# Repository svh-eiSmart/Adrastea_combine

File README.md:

# Adrastea_combine
Combine Sensor Featherwings data with I2C and SPI to transmit via MQTT to Azure

Current Progress - All I2C sensor driver integration (HIDS, TIDS, ITDS and PADS) for sensor featherwing with basic porting for delay

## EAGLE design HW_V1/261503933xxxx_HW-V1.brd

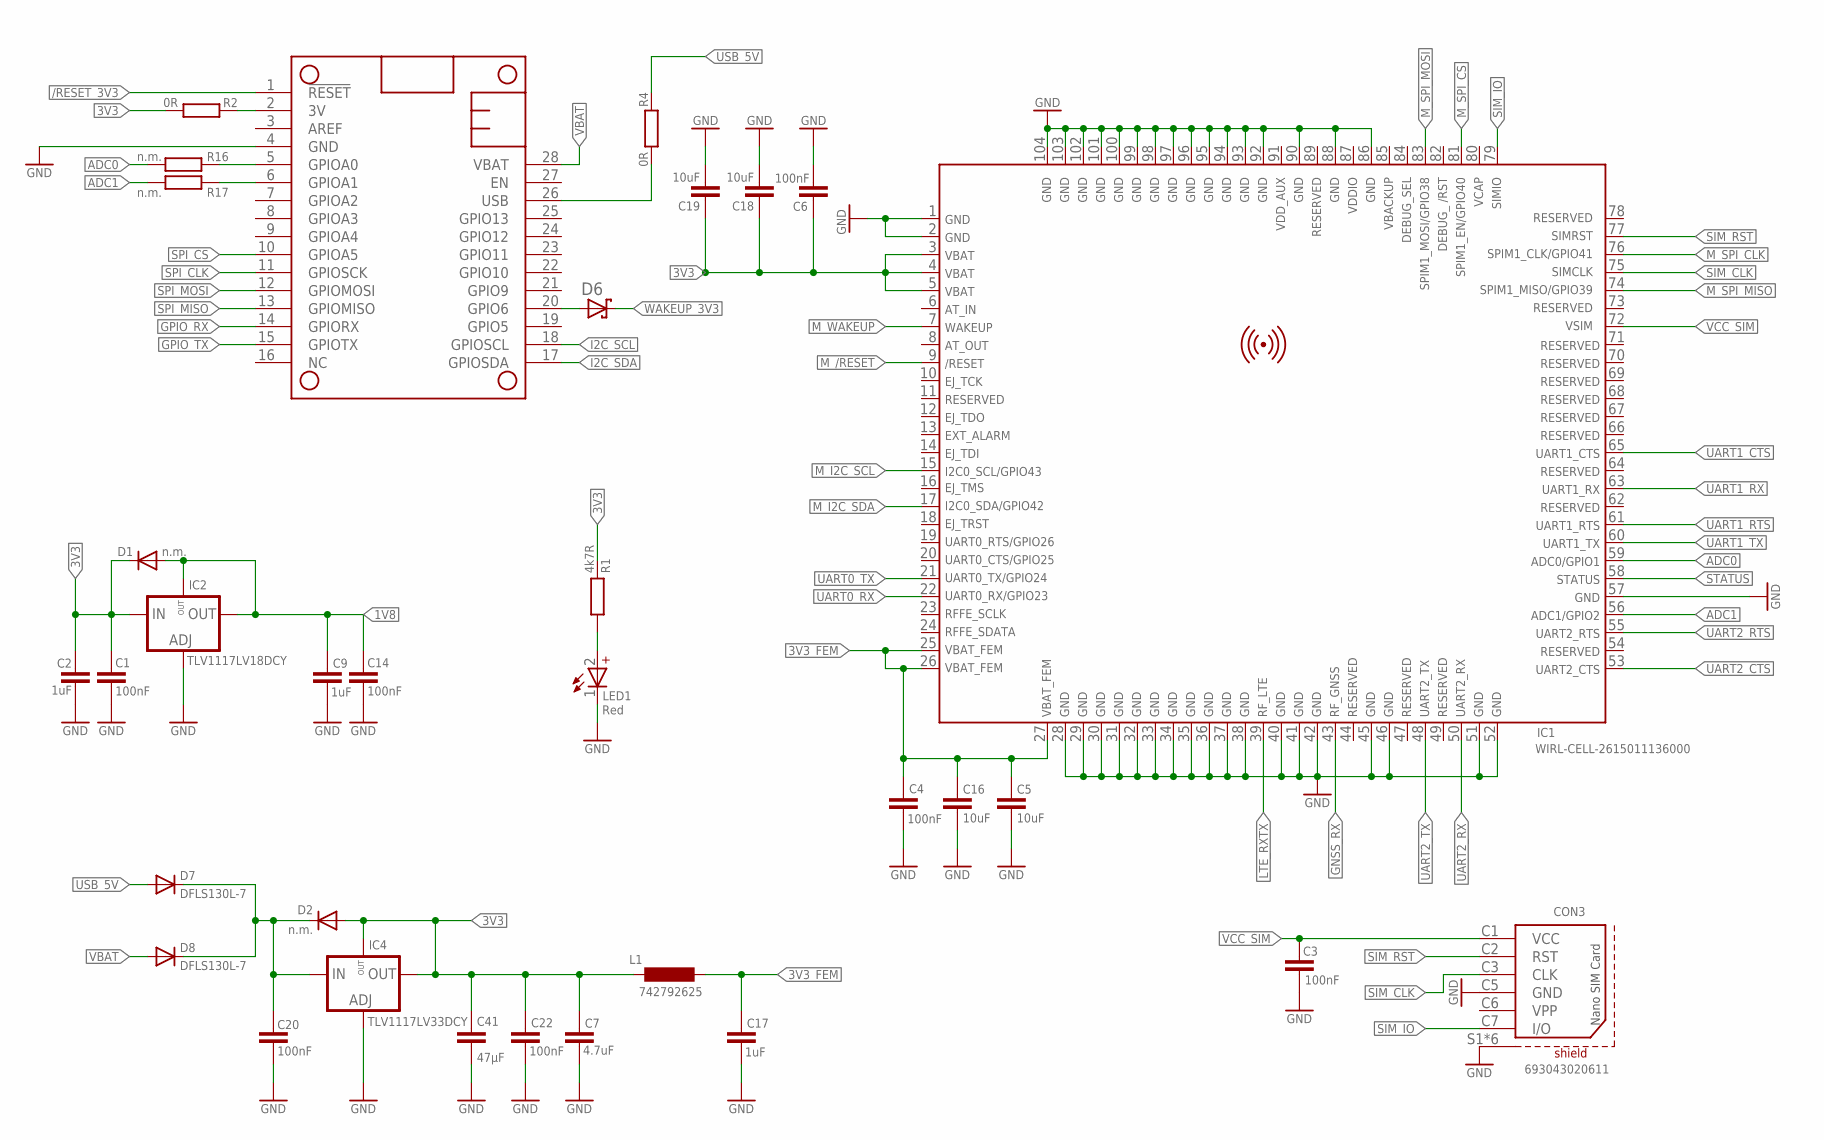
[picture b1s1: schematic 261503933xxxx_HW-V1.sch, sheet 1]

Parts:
C1, C3, C4, C6, C14, C20, C22: 100nF; C0402_IPC
C2, C9, C17: 1uF; C0402_IPC
C5, C16, C18, C19: 10uF; C0402_IPC
C7: 4.7uF; C0402_IPC
C41: 47µF; C0805
CON3: 693043020611
D1, D2: n.m.; SOT23@1
D6: BAT540402_X1-DFN1006-2; X1-DFN1006-2
D7, D8: DFLS130L-7; SOD123_POWERDI
IC1: WIRL-CELL-2615011136000
IC2: TLV1117LV18DCY; SOT223-4
IC4: TLV1117LV33DCY; SOT223-4
L1: 742792625; L0603_WE-MK
LED1: Red; WL-SMSW_1204_A
MS1: FEATHERWING_80MM
R1: 4k7R; R0402_IPC
R2, R4: 0R; R0603_IPC
R16, R17: n.m.; R0402_IPC

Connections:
1V8: C9.1, C14.2, D1.1 (A), IC2.2 (OUT), IC2.4 (OUT); also elsewhere on the board
3V: MS1.2 (3V), R2.2
3V3: C1.2, C2.1, C6.2, C7.1, C18.1, C19.1, C22.2, C41.P$1 (1), D1.3 (C), D2.1 (A), IC1.3 (VBAT), IC1.4 (VBAT), IC1.5 (VBAT), IC2.3 (IN), IC4.2 (OUT), IC4.4 (OUT), L1.1, R1.2, R2.1; also elsewhere on the board
3V3_FEM: C4.2, C5.1, C16.1, C17.1, IC1.25 (VBAT_FEM), IC1.26 (VBAT_FEM), IC1.27 (VBAT_FEM), L1.2
5V_IN: C20.2, D2.3 (C), D7.K (C), D8.K (C), IC4.3 (IN)
/RESET_3V3: MS1.1 (!RESET); also elsewhere on the board
ADC0: IC1.59 (ADC0/GPIO1), R16.1
ADC1: IC1.56 (ADC1/GPIO2), R17.1
ADC_0: MS1.5 (GPIOA0), R16.2
ADC_1: MS1.6 (GPIOA1), R17.2
FEATHER_USB: MS1.26 (USB), R4.1
GND: C1.1, C2.2, C3.2, C4.1, C5.2, C6.1, C7.2, C9.2, C14.1, C16.2, C17.2, C18.2, C19.2, C20.1, C22.1, C41.P$2 (2), CON3.C5 (GND), CON3.S1 (SHIELD), CON3.S2 (SHIELD), CON3.S3 (SHIELD), CON3.S4 (SHIELD), CON3.S5 (SHIELD), CON3.S6 (SHIELD), IC1.1 (GND), IC1.2 (GND), IC1.28 (GND), IC1.29 (GND), IC1.30 (GND), IC1.31 (GND), IC1.32 (GND), IC1.33 (GND), IC1.34 (GND), IC1.35 (GND), IC1.36 (GND), IC1.37 (GND), IC1.38 (GND), IC1.40 (GND), IC1.41 (GND), IC1.42 (GND), IC1.45 (GND), IC1.46 (GND), IC1.51 (GND), IC1.52 (GND), IC1.57 (GND), IC1.86 (GND), IC1.88 (GND), IC1.90 (GND), IC1.92 (GND), IC1.93 (GND), IC1.94 (GND), IC1.95 (GND), IC1.96 (GND), IC1.97 (GND), IC1.98 (GND), IC1.99 (GND), IC1.100 (GND), IC1.101 (GND), IC1.102 (GND), IC1.103 (GND), IC1.104 (GND), IC2.1 (ADJ), IC4.1 (ADJ), LED1.1 (-), MS1.4 (GND); also elsewhere on the board
GNSS_RX: IC1.43 (RF_GNSS_ANT); also elsewhere on the board
GPIO_RX: MS1.14 (GPIORX); also elsewhere on the board
GPIO_TX: MS1.15 (GPIOTX); also elsewhere on the board
I2C_SCL: MS1.18 (GPIOSCL); also elsewhere on the board
I2C_SDA: MS1.17 (GPIOSDA); also elsewhere on the board
LTE_RXTX: IC1.39 (RF_RXTX); also elsewhere on the board
M_/RESET: IC1.9 (/RESET); also elsewhere on the board
M_I2C_SCL: IC1.15 (I2C0_SCL/GPIO43); also elsewhere on the board
M_I2C_SDA: IC1.17 (I2C0_SDA/GPIO42); also elsewhere on the board
M_SPI_CLK: IC1.76 (SPIM1_CLK/GPIO41); also elsewhere on the board
M_SPI_CS: IC1.81 (SPIM1_EN/GPIO40); also elsewhere on the board
M_SPI_MISO: IC1.74 (SPIM1_MISO/GPIO39); also elsewhere on the board
M_SPI_MOSI: IC1.83 (SPIM1_MOSI/GPIO38); also elsewhere on the board
M_WAKEUP: IC1.7 (WAKEUP); also elsewhere on the board
unnamed: LED1.2 (+), R1.1
unnamed: D6.2 (A), MS1.20 (GPIO6)
SIM_CLK: CON3.C3 (CLK), IC1.75 (SIMCLK)
SIM_IO: CON3.C7 (I/O), IC1.79 (SIMIO)
SIM_RST: CON3.C2 (RST), IC1.77 (SIMRST)
SPI_CLK: MS1.11 (GPIOSCK); also elsewhere on the board
SPI_CS: MS1.10 (GPIOA5); also elsewhere on the board
SPI_MISO: MS1.13 (GPIOMISO); also elsewhere on the board
SPI_MOSI: MS1.12 (GPIOMOSI); also elsewhere on the board
STATUS: IC1.58 (STATUS); also elsewhere on the board
UART0_RX: IC1.22 (UART0_RX/GPIO23); also elsewhere on the board
UART0_TX: IC1.21 (UART0_TX/GPIO24); also elsewhere on the board
UART1_CTS: IC1.65 (UART1_CTS); also elsewhere on the board
UART1_RTS: IC1.61 (UART1_RTS); also elsewhere on the board
UART1_RX: IC1.63 (UART1_RX); also elsewhere on the board
UART1_TX: IC1.60 (UART1_TX); also elsewhere on the board
UART2_CTS: IC1.53 (UART2_CTS); also elsewhere on the board
UART2_RTS: IC1.55 (UART2_RTS); also elsewhere on the board
UART2_RX: IC1.50 (UART2_RX); also elsewhere on the board
UART2_TX: IC1.48 (UART2_TX); also elsewhere on the board
USB_5V: D7.A, R4.2; also elsewhere on the board
VBAT: D8.A, MS1.28 (VBAT); also elsewhere on the board
VCC_SIM: C3.1, CON3.C1 (VCC), IC1.72 (VSIM)
WAKEUP_3V3: D6.1 (C); also elsewhere on the board

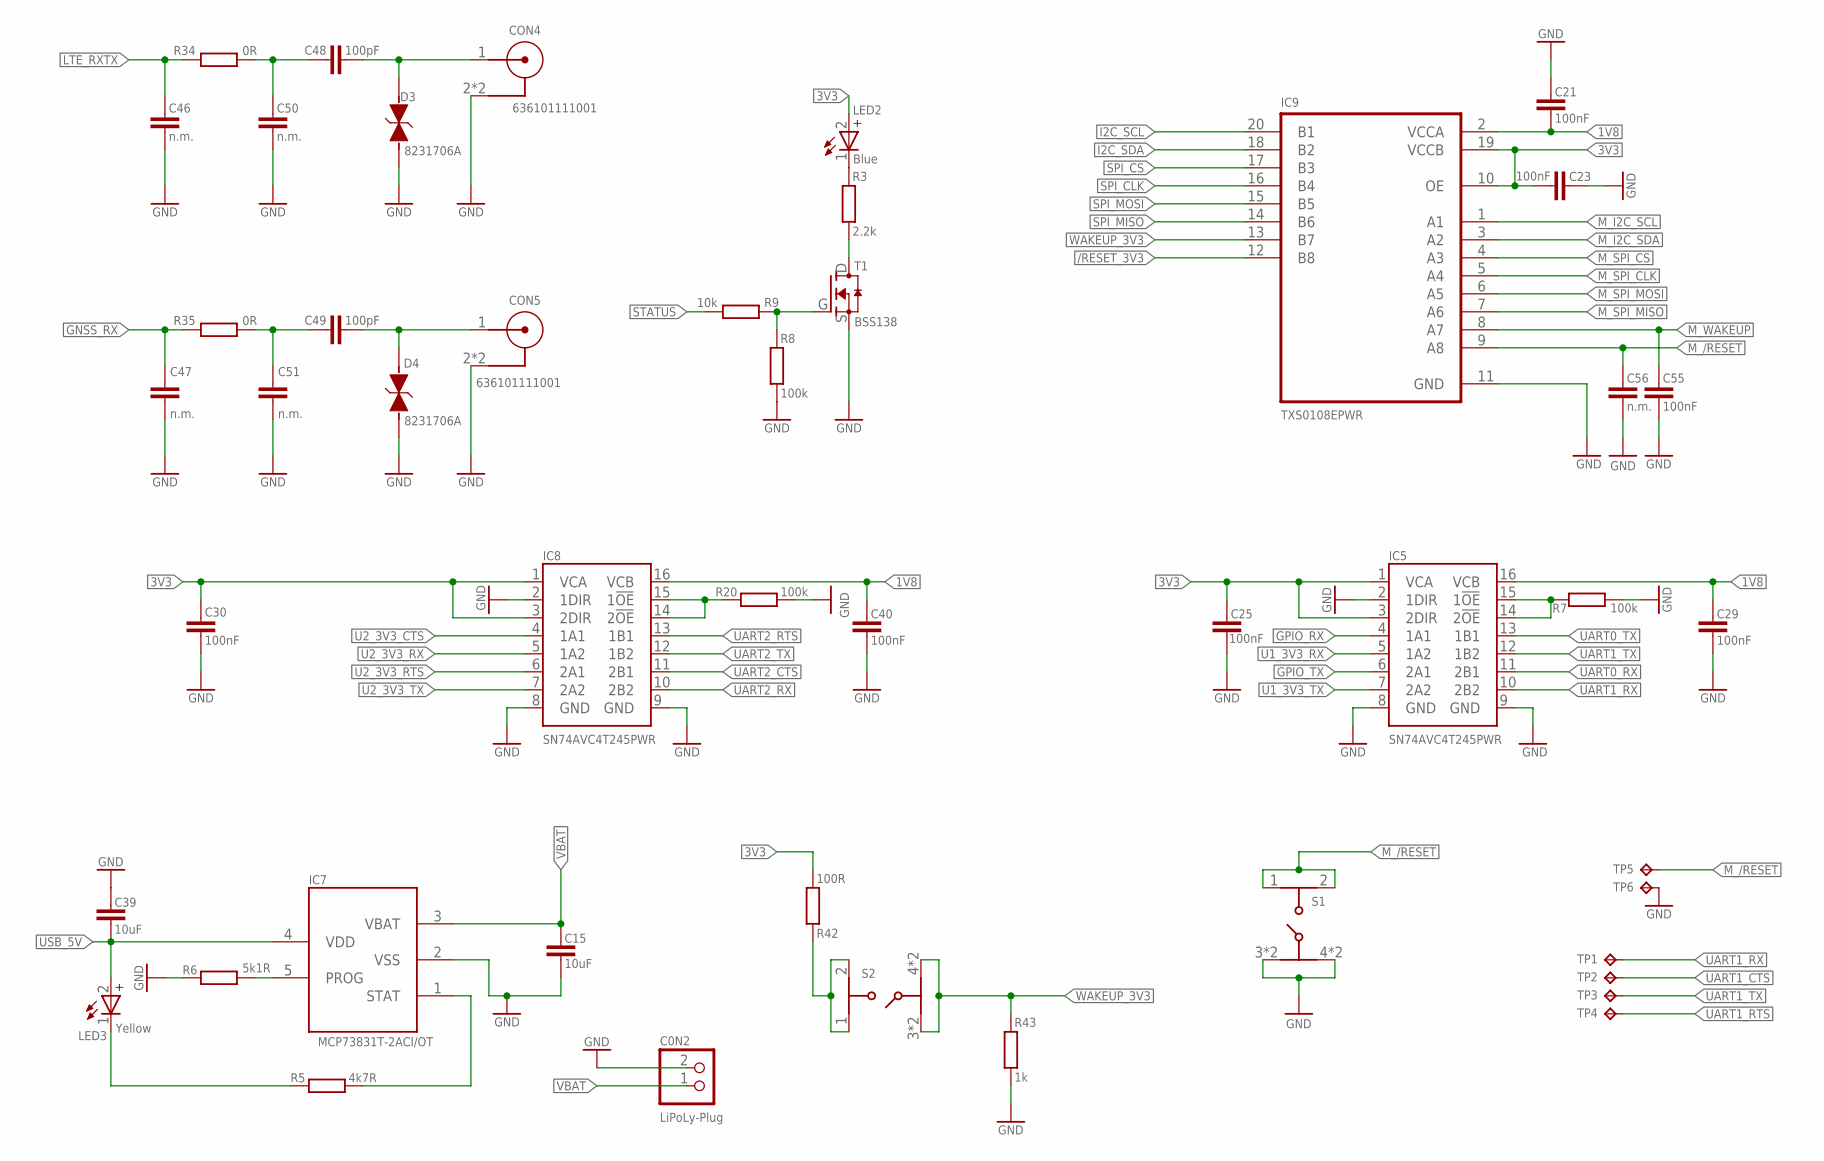
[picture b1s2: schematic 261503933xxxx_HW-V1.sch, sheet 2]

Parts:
C0N2: LiPoLy-Plug; JST-PH-2-SMT-RA-ADRASTEA-ANGEPASST
C15: 10uF; C0402_IPC
C21, C23, C25, C29, C30, C40, C55: 100nF; C0402_IPC
C39: 10uF; C0603_IPC
C46, C47, C50, C51, C56: n.m.; C0402_IPC
C48, C49: 100pF; C0402_IPC
CON4, CON5: 636101111001
D3, D4: 8231706A; WE-VE_FEMTOF_0402
IC5, IC8: SN74AVC4T245PWR; PW16(TSSOP16)
IC7: MCP73831T-2ACI/OT; SOT23-5
IC9: TXS0108EPWR; SOP65P640X120-20N
LED2: Blue; WL-SMSW_1204_A
LED3: Yellow; WL-SMSW_1204_A
R3: 2.2k; R0402_IPC
R5: 4k7R; R0402_IPC
R6: 5k1R; R0402_IPC
R7, R8, R20: 100k; R0402_IPC
R9: 10k; R0402_IPC
R34, R35: 0R; R0402_IPC
R42: 100R; R0402_IPC
R43: 1k; R0402_IPC
S1, S2: 434331013822
T1: BSS138
TP1, TP2, TP3, TP4, TP5, TP6: TP15R

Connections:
1V8: C21.1, C29.2, C40.2, IC5.16 (VCB), IC8.16 (VCB), IC9.2 (VCCA); also elsewhere on the board
3V3: C23.1, C25.2, C30.2, IC5.1 (VCA), IC5.3 (2DIR), IC8.1 (VCA), IC8.3 (2DIR), IC9.10 (OE), IC9.19 (VCCB), LED2.2 (+), R42.1; also elsewhere on the board
/RESET_3V3: IC9.12 (B8); also elsewhere on the board
GND: C0N2.2 (1), C15.2, C21.2, C23.2, C25.1, C29.1, C30.1, C39.1, C40.1, C46.1, C47.1, C50.1, C51.1, C55.1, C56.1, CON4.2, CON4.3 (2), CON5.2, CON5.3 (2), D3.2, D4.2, IC5.2 (1DIR), IC5.8 (GND), IC5.9 (GND), IC7.2 (VSS), IC8.2 (1DIR), IC8.8 (GND), IC8.9 (GND), IC9.11 (GND), R6.1, R7.2, R8.2, R20.2, R43.2, S1.3, S1.4, S1.5 (3), S1.6 (4), T1.S, TP6.P$1; also elsewhere on the board
GNSS_RX: C47.2, R35.2; also elsewhere on the board
GPIO_RX: IC5.4 (1A1); also elsewhere on the board
GPIO_TX: IC5.6 (2A1); also elsewhere on the board
I2C_SCL: IC9.20 (B1); also elsewhere on the board
I2C_SDA: IC9.18 (B2); also elsewhere on the board
LS_ISO_CTRL1: IC8.14 (2!OE), IC8.15 (1!OE), R20.1
LTE_RXTX: C46.2, R34.2; also elsewhere on the board
M_/RESET: C56.2, IC9.9 (A8), S1.1, S1.2, TP5.P$1; also elsewhere on the board
M_I2C_SCL: IC9.1 (A1); also elsewhere on the board
M_I2C_SDA: IC9.3 (A2); also elsewhere on the board
M_SPI_CLK: IC9.5 (A4); also elsewhere on the board
M_SPI_CS: IC9.4 (A3); also elsewhere on the board
M_SPI_MISO: IC9.7 (A6); also elsewhere on the board
M_SPI_MOSI: IC9.6 (A5); also elsewhere on the board
M_WAKEUP: C55.2, IC9.8 (A7); also elsewhere on the board
unnamed: LED2.1 (-), R3.1
unnamed: C49.1, CON5.1, D4.1
unnamed: C48.1, CON4.1, D3.1
unnamed: R42.2, S2.1, S2.2
unnamed: C48.2, C50.2, R34.1
unnamed: R3.2, T1.D
unnamed: C49.2, C51.2, R35.1
unnamed: R8.1, R9.2, T1.G
unnamed: LED3.1 (-), R5.1
unnamed: IC7.5 (PROG), R6.2
unnamed: IC5.14 (2!OE), IC5.15 (1!OE), R7.1
SPI_CLK: IC9.16 (B4); also elsewhere on the board
SPI_CS: IC9.17 (B3); also elsewhere on the board
SPI_MISO: IC9.14 (B6); also elsewhere on the board
SPI_MOSI: IC9.15 (B5); also elsewhere on the board
STAT: IC7.1 (STAT), R5.2
STATUS: R9.1; also elsewhere on the board
U1_3V3_RX: IC5.5 (1A2); also elsewhere on the board
U1_3V3_TX: IC5.7 (2A2); also elsewhere on the board
U2_3V3_CTS: IC8.4 (1A1); also elsewhere on the board
U2_3V3_RTS: IC8.6 (2A1); also elsewhere on the board
U2_3V3_RX: IC8.5 (1A2); also elsewhere on the board
U2_3V3_TX: IC8.7 (2A2); also elsewhere on the board
UART0_RX: IC5.11 (2B1); also elsewhere on the board
UART0_TX: IC5.13 (1B1); also elsewhere on the board
UART1_CTS: TP2.P$1; also elsewhere on the board
UART1_RTS: TP4.P$1; also elsewhere on the board
UART1_RX: IC5.10 (2B2), TP1.P$1; also elsewhere on the board
UART1_TX: IC5.12 (1B2), TP3.P$1; also elsewhere on the board
UART2_CTS: IC8.11 (2B1); also elsewhere on the board
UART2_RTS: IC8.13 (1B1); also elsewhere on the board
UART2_RX: IC8.10 (2B2); also elsewhere on the board
UART2_TX: IC8.12 (1B2); also elsewhere on the board
USB_5V: C39.2, IC7.4 (VDD), LED3.2 (+); also elsewhere on the board
VBAT: C0N2.1 (2), C15.1, IC7.3 (VBAT); also elsewhere on the board
WAKEUP_3V3: IC9.13 (B7), R43.1, S2.3, S2.4, S2.5 (3), S2.6 (4); also elsewhere on the board

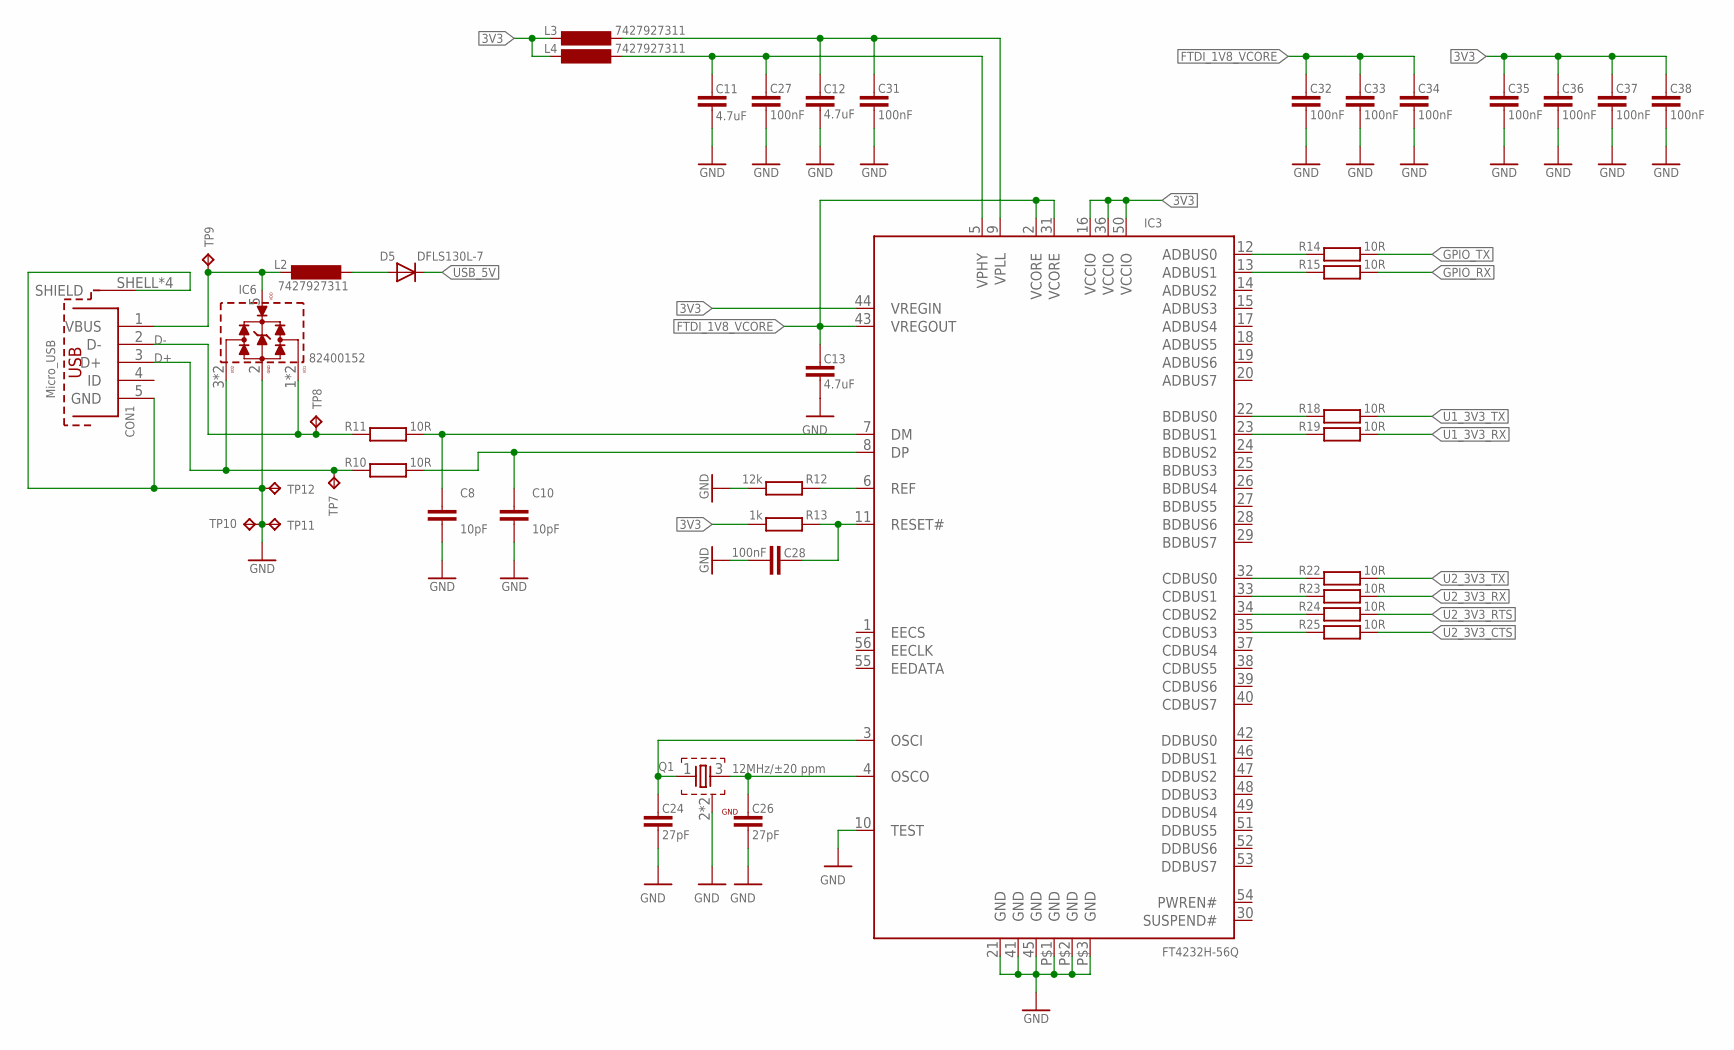
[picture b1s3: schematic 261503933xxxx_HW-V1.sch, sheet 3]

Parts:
C8, C10: 10pF; C0402_IPC
C11, C12, C13: 4.7uF; C0402_IPC
C24, C26: 27pF; C0402_IPC
C27, C28, C31, C32, C33, C34, C35, C36, C37, C38: 100nF; C0402_IPC
CON1: Micro_USB; 629105150521
D5: DFLS130L-7; SOD123_POWERDI
IC3: FT4232H-56Q; VQFN-56
IC6: 82400152; WE-TVS_SOT563
L2, L3, L4: 7427927311; L0402_WE-MK
Q1: 12MHz/±20 ppm; WE-XTAL_CFPX-180
R10, R11, R14, R15, R18, R19, R22, R23, R24, R25: 10R; R0402_IPC
R12: 12k; R0402_IPC
R13: 1k; R0402_IPC
TP7, TP8, TP9, TP10, TP11, TP12: TP15R

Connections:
3V3: C35.2, C36.2, C37.2, C38.2, IC3.16 (VCCIO), IC3.36 (VCCIO), IC3.44 (VREGIN), IC3.50 (VCCIO), L3.P$2 (2), L4.P$2 (2), R13.1; also elsewhere on the board
D+: CON1.3 (D+), IC6.3 (I/O2), IC6.4 (I/O2), R10.1, TP7.P$1
D-: CON1.2 (D-), IC6.1 (I/O1), IC6.6 (I/O1), R11.2, TP8.P$1
FTDI_1V8_VCORE: C13.1, C32.2, C33.2, C34.2, IC3.2 (VCORE), IC3.31 (VCORE), IC3.43 (VREGOUT)
FTDI_CTS#_CH-C: IC3.35 (CDBUS3), R25.1
FTDI_RESET: C28.2, IC3.11 (RESET#), R13.2
FTDI_RTS#_CH-C: IC3.34 (CDBUS2), R24.1
FTDI_RXD_CH-A: IC3.13 (ADBUS1), R15.1
FTDI_RXD_CH-B: IC3.23 (BDBUS1), R19.1
FTDI_RXD_CH-C: IC3.33 (CDBUS1), R23.1
FTDI_TXD_CH-A: IC3.12 (ADBUS0), R14.1
FTDI_TXD_CH-B: IC3.22 (BDBUS0), R18.1
FTDI_TXD_CH-C: IC3.32 (CDBUS0), R22.1
GND: C8.1, C10.1, C11.2, C12.2, C13.2, C24.1, C26.1, C27.1, C28.1, C31.1, C32.1, C33.1, C34.1, C35.1, C36.1, C37.1, C38.1, CON1.5 (GND), CON1.SHELL (SHIELD), CON1.SHELL1 (SHIELD), CON1.SHELL2 (SHIELD), CON1.SHELL3 (SHIELD), IC3.10 (TEST), IC3.21 (GND), IC3.41 (GND), IC3.45 (GND), IC3.P$1 (GND), IC3.P$2 (GND), IC3.P$3 (GND), IC6.2 (GND), Q1.2 (GND), Q1.4 (GND), R12.1, TP10.P$1, TP11.P$1, TP12.P$1; also elsewhere on the board
GPIO_RX: R15.2; also elsewhere on the board
GPIO_TX: R14.2; also elsewhere on the board
unnamed: C8.2, IC3.7 (DM), R11.1
unnamed: C10.2, IC3.8 (DP), R10.2
unnamed: D5.A, L2.P$1 (1)
unnamed: C11.1, C27.2, IC3.5 (VPHY), L4.P$1 (1)
unnamed: C12.1, C31.2, IC3.9 (VPLL), L3.P$1 (1)
unnamed: IC3.6 (REF), R12.2
unnamed: C24.2, IC3.3 (OSCI), Q1.1
unnamed: C26.2, IC3.4 (OSCO), Q1.3 (2)
U1_3V3_RX: R19.2; also elsewhere on the board
U1_3V3_TX: R18.2; also elsewhere on the board
U2_3V3_CTS: R25.2; also elsewhere on the board
U2_3V3_RTS: R24.2; also elsewhere on the board
U2_3V3_RX: R23.2; also elsewhere on the board
U2_3V3_TX: R22.2; also elsewhere on the board
USB_5V: D5.K (C); also elsewhere on the board
VBUS: CON1.1 (VBUS), IC6.5 (VDD), L2.P$2 (2), TP9.P$1

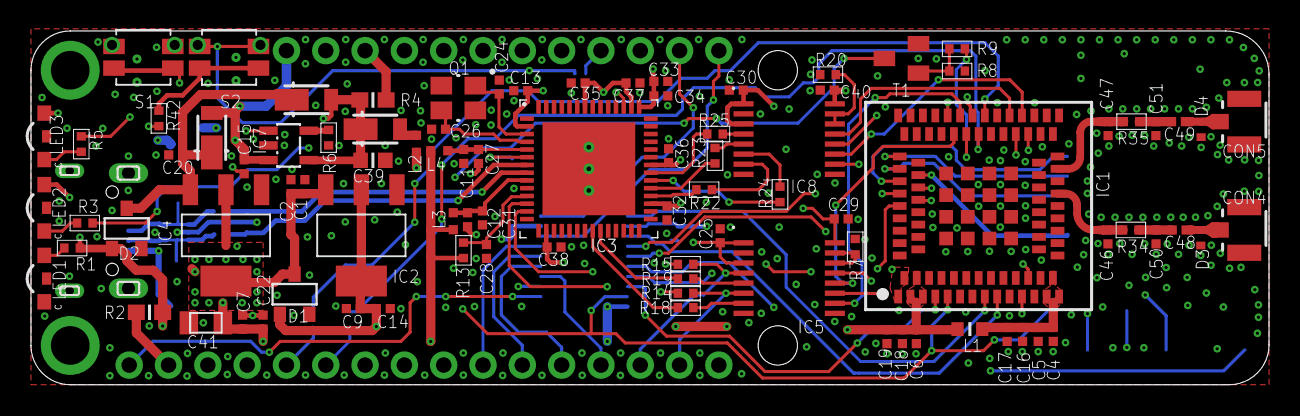
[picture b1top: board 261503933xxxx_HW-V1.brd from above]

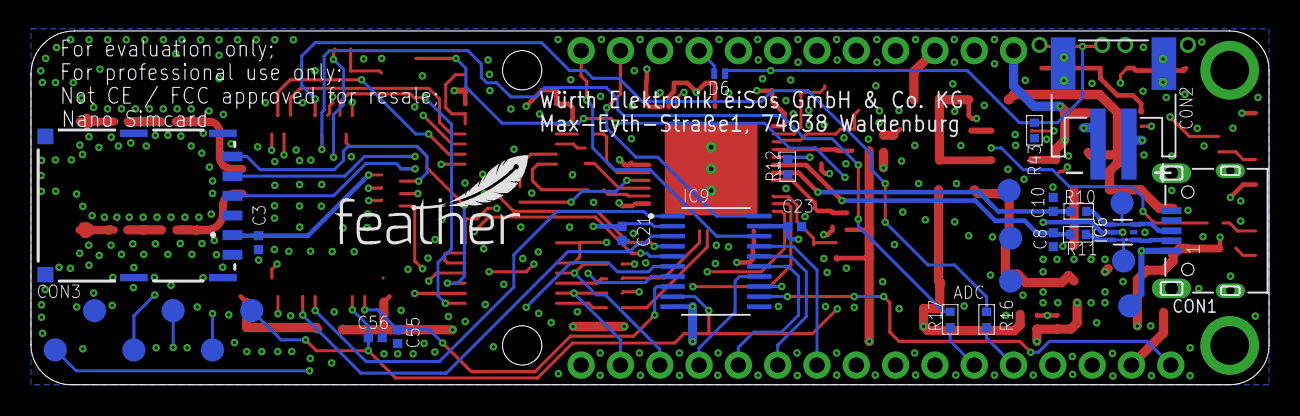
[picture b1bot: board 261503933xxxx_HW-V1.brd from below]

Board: 4 copper layers, 79.9 x 22.7 mm, 124 parts (32 on the bottom side), 90 nets.

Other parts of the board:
U$4: FEATHER_12MM

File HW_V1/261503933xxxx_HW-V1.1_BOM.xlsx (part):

Part | Value | NR | MANUFACTURER | COMMENT | Device | Package | Description | CCH-TYP | COMMENT2 | DATASHEET-URL | DESCRIPTION3 | GENDER | GERDER | HEIGHT | HERSTELLER | ILEAK | ISAT | Spalte4 | MANUFACTURER2 | MAT | MF | MOUNT | MP | Spalte5 | NR2 | P | PACK | PACKAGE6 | PART-NUMBER | PINS | PRICE | RDC | SPG | TEMP | TOL | TYPE | VALUE | VCH-TYP | VESD-AIR | VESD-CONTACT | Z
C0N2 | LiPoLy-Plug | 1769 | Adafruit |  | JST_2PIN | JST-PH-2-SMT-RA-ADRASTEA-ANGEPASST | JST 2-Pin Connectors of various flavors |  |  |  |  |  |  | 9mm |  |  |  |  |  |  |  |  |  |  |  |  | SMT
C1 | 100nF | 885012205037 | Würth Elektronik |  | C0402_IPC | C0402_IPC |  |  |  |  |  |  |  | 0.5mm |  |  |  |  |  | X7R |  |  |  |  |  |  | 402 |  |  |  |  |  | 16V |  | 0.1
C10 | 10pF | 885012005055 | Würth Elektronik |  | C10PF0402_IPC | C0402_IPC |  |  |  |  |  |  |  | 0.5mm |  |  |  |  |  | NP0 |  |  |  |  |  |  | 402 |  |  |  |  |  | 50V |  | 0.05
C11 | 4.7uF | 885012105008 | Würth Elektronik |  | C4.7UF0402_IPC | C0402_IPC |  |  |  |  |  |  |  | 0.5mm |  |  |  |  |  | X5R |  |  |  |  |  |  | 402 |  |  |  |  |  | 6.3V |  | 0.2
C12 | 4.7uF | 885012105008 | Würth Elektronik |  | C4.7UF0402_IPC | C0402_IPC |  |  |  |  |  |  |  | 0.5mm |  |  |  |  |  | X5R |  |  |  |  |  |  | 402 |  |  |  |  |  | 6.3V |  | 0.2
C13 | 4.7uF | 885012105008 | Würth Elektronik |  | C4.7UF0402_IPC | C0402_IPC |  |  |  |  |  |  |  | 0.5mm |  |  |  |  |  | X5R |  |  |  |  |  |  | 402 |  |  |  |  |  | 6.3V |  | 0.2
C14 | 100nF | 885012205037 | Würth Elektronik |  | C0402_IPC | C0402_IPC |  |  |  |  |  |  |  | 0.5mm |  |  |  |  |  | X7R |  |  |  |  |  |  | 402 |  |  |  |  |  | 16V |  | 0.1
C15 | 10uF | 885012105020 | Würth Elektronik |  | C10UF0402_IPC | C0402_IPC |  |  |  |  |  |  |  | 0.5mm |  |  |  |  |  | X5R |  |  |  |  |  |  | 402 |  |  |  |  |  | 6.3V | -55 to +85°c | 0.2
C16 | 10uF | 885012105020 | Würth Elektronik |  | C0402_IPC | C0402_IPC |  |  |  |  |  |  |  | 0.5mm |  |  |  |  |  | X5R | 0.2 |  |  |  |  |  | 402 |  |  |  |  |  | 6,3V |  | 0.2
C17 | 1uF | 885012105012 | Würth Elektronik |  | C1UF0402_IPC | C0402_IPC |  |  |  |  |  |  |  | 0.5mm |  |  |  |  |  | X5R |  |  |  |  |  |  | 402 |  |  |  |  |  | 10V |  | 0.2
C18 | 10uF | 885012105020 | Würth Elektronik |  | C0402_IPC | C0402_IPC |  |  |  |  |  |  |  | 0.5mm |  |  |  |  |  | X5R | 0.2 |  |  |  |  |  | 402 |  |  |  |  |  | 6,3V |  | 0.2
C19 | 10uF | 885012105020 | Würth Elektronik |  | C0402_IPC | C0402_IPC |  |  |  |  |  |  |  | 0.5mm |  |  |  |  |  | X5R | 0.2 |  |  |  |  |  | 402 |  |  |  |  |  | 6,3V |  | 0.2
C2 | 1uF | 885012105012 | Würth Elektronik |  | C1UF0402_IPC | C0402_IPC |  |  |  |  |  |  |  | 0.5mm |  |  |  |  |  | X5R |  |  |  |  |  |  | 402 |  |  |  |  |  | 10V |  | 0.2
C20 | 100nF | 885012205037 | Würth Elektronik |  | C0402_IPC | C0402_IPC |  |  |  |  |  |  |  | 0.5mm |  |  |  |  |  | X7R |  |  |  |  |  |  | 402 |  |  |  |  |  | 16V |  | 0.1
C21 | 100nF | 885012205037 | Würth Elektronik |  | C0402_IPC | C0402_IPC |  |  |  |  |  |  |  | 0.5mm |  |  |  |  |  | X7R |  |  |  |  |  |  | 402 |  |  |  |  |  | 16V |  | 0.1
C22 | 100nF | 885012205037 | Würth Elektronik |  | C0402_IPC | C0402_IPC |  |  |  |  |  |  |  | 0.5mm |  |  |  |  |  | X7R |  |  |  |  |  |  | 402 |  |  |  |  |  | 16V |  | 0.1
C23 | 100nF | 885012205037 | Würth Elektronik |  | C0402_IPC | C0402_IPC |  |  |  |  |  |  |  | 0.5mm |  |  |  |  |  | X7R |  |  |  |  |  |  | 402 |  |  |  |  |  | 16V |  | 0.1
C24 | 27pF | CL05C270JB5NNNC | Samsung |  | C27P0402_IPC | C0402_IPC |  |  |  |  |  |  |  | 0.5mm |  |  |  |  |  | C0G |  |  |  |  |  |  | 402 |  |  |  |  |  | 50V |  | 0.05
C25 | 100nF | 885012205037 | Würth Elektronik |  | C0402_IPC | C0402_IPC |  |  |  |  |  |  |  | 0.5mm |  |  |  |  |  | X7R |  |  |  |  |  |  | 402 |  |  |  |  |  | 16V |  | 0.1
C26 | 27pF | CL05C270JB5NNNC | Samsung |  | C27P0402_IPC | C0402_IPC |  |  |  |  |  |  |  | 0.5mm |  |  |  |  |  | C0G |  |  |  |  |  |  | 402 |  |  |  |  |  | 50V |  | 0.05
C27 | 100nF | 885012205037 | Würth Elektronik |  | C0402_IPC | C0402_IPC |  |  |  |  |  |  |  | 0.5mm |  |  |  |  |  | X7R |  |  |  |  |  |  | 402 |  |  |  |  |  | 16V |  | 0.1
C28 | 100nF | 885012205037 | Würth Elektronik |  | C0402_IPC | C0402_IPC |  |  |  |  |  |  |  | 0.5mm |  |  |  |  |  | X7R |  |  |  |  |  |  | 402 |  |  |  |  |  | 16V |  | 0.1
C29 | 100nF | 885012205037 | Würth Elektronik |  | C0402_IPC | C0402_IPC |  |  |  |  |  |  |  | 0.5mm |  |  |  |  |  | X7R |  |  |  |  |  |  | 402 |  |  |  |  |  | 16V |  | 0.1
C3 | 100nF | 885012205037 | Würth Elektronik |  | C100NF0402_IPC | C0402_IPC |  |  |  |  |  |  |  | 0.5mm |  |  |  |  |  | X7R |  |  |  |  |  |  | 402 |  |  |  |  |  | 16V | -55 to +125°C | 0.1
C30 | 100nF | 885012205037 | Würth Elektronik |  | C0402_IPC | C0402_IPC |  |  |  |  |  |  |  | 0.5mm |  |  |  |  |  | X7R |  |  |  |  |  |  | 402 |  |  |  |  |  | 16V |  | 0.1
C31 | 100nF | 885012205037 | Würth Elektronik |  | C0402_IPC | C0402_IPC |  |  |  |  |  |  |  | 0.5mm |  |  |  |  |  | X7R |  |  |  |  |  |  | 402 |  |  |  |  |  | 16V |  | 0.1
C32 | 100nF | 885012205037 | Würth Elektronik |  | C0402_IPC | C0402_IPC |  |  |  |  |  |  |  | 0.5mm |  |  |  |  |  | X7R |  |  |  |  |  |  | 402 |  |  |  |  |  | 16V |  | 0.1
C33 | 100nF | 885012205037 | Würth Elektronik |  | C0402_IPC | C0402_IPC |  |  |  |  |  |  |  | 0.5mm |  |  |  |  |  | X7R |  |  |  |  |  |  | 402 |  |  |  |  |  | 16V |  | 0.1
C34 | 100nF | 885012205037 | Würth Elektronik |  | C0402_IPC | C0402_IPC |  |  |  |  |  |  |  | 0.5mm |  |  |  |  |  | X7R |  |  |  |  |  |  | 402 |  |  |  |  |  | 16V |  | 0.1
C35 | 100nF | 885012205037 | Würth Elektronik |  | C0402_IPC | C0402_IPC |  |  |  |  |  |  |  | 0.5mm |  |  |  |  |  | X7R |  |  |  |  |  |  | 402 |  |  |  |  |  | 16V |  | 0.1
C36 | 100nF | 885012205037 | Würth Elektronik |  | C0402_IPC | C0402_IPC |  |  |  |  |  |  |  | 0.5mm |  |  |  |  |  | X7R |  |  |  |  |  |  | 402 |  |  |  |  |  | 16V |  | 0.1
C37 | 100nF | 885012205037 | Würth Elektronik |  | C0402_IPC | C0402_IPC |  |  |  |  |  |  |  | 0.5mm |  |  |  |  |  | X7R |  |  |  |  |  |  | 402 |  |  |  |  |  | 16V |  | 0.1
C38 | 100nF | 885012205037 | Würth Elektronik |  | C0402_IPC | C0402_IPC |  |  |  |  |  |  |  | 0.5mm |  |  |  |  |  | X7R |  |  |  |  |  |  | 402 |  |  |  |  |  | 16V |  | 0.1
C39 | 10uF | 885012106031 | Wurth Elektronik |  | C1UF0603_IPC | C0603_IPC |  |  |  |  |  |  |  | 0.8mm |  |  |  |  |  | X5R |  |  |  |  |  |  | 603 |  |  |  |  |  | 25V |  | 0.1
C4 | 100nF | 885012205037 | Würth Elektronik |  | C0402_IPC | C0402_IPC |  |  |  |  |  |  |  | 0.5mm |  |  |  |  |  | X7R |  |  |  |  |  |  | 402 |  |  |  |  |  | 16V |  | 0.1
C40 | 100nF | 885012205037 | Würth Elektronik |  | C0402_IPC | C0402_IPC |  |  |  |  |  |  |  | 0.5mm |  |  |  |  |  | X7R |  |  |  |  |  |  | 402 |  |  |  |  |  | 16V |  | 0.1
C41 | 47µF | 885012107006 | Wurth Elektronik |  | C47UF0805 | C0805 |  |  |  |  |  |  |  | 1.25mm |  |  |  |  |  | X7R |  |  |  |  |  |  | 805 |  |  |  |  |  | 6.3V |  | 0.2
C46 | n.m. | n.m. | n.m. |  | C0402_IPC | C0402_IPC |  |  |  |  |  |  |  | 0.5mm |  |  |  |  |  |  |  |  |  |  |  |  | 402
C47 | n.m. | n.m. | n.m. |  | C0402_IPC | C0402_IPC |  |  |  |  |  |  |  | 0.5mm |  |  |  |  |  |  |  |  |  |  |  |  | 402
C48 | 100pF | 885012005061 | Würth Elektronik |  | C100PF0402_IPC | C0402_IPC |  |  |  |  |  |  |  | 0.5mm |  |  |  |  |  | NP0 |  |  |  |  |  |  | 402 |  |  |  |  |  | 50V |  | 0.05
C49 | 100pF | 885012005061 | Würth Elektronik |  | C0402_IPC | C0402_IPC |  |  |  |  |  |  |  | 0.5mm |  |  |  |  |  | NP0 |  |  |  |  |  |  | 402 |  |  |  |  |  | 50V |  | 0.05
C5 | 10uF | 885012105020 | Würth Elektronik |  | C0402_IPC | C0402_IPC |  |  |  |  |  |  |  | 0.5mm |  |  |  |  |  | X5R | 0.2 |  |  |  |  |  | 402 |  |  |  |  |  | 6,3V |  | 0.2
C50 | n.m. | n.m. | n.m. |  | C0402_IPC | C0402_IPC |  |  |  |  |  |  |  | 0.5mm |  |  |  |  |  |  |  |  |  |  |  |  | 402
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
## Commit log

2023-06-16 Working I2C of TIDS unsure of SPI with PADS and ITDS
2023-06-27 Working I2C of all sensors I2C - TIDS, PADS and ITDS
2023-07-25 Working I2C of all sensors I2C - TIDS, PADS, ITDS and HIDS with basic porting of delay
2023-07-25 Working I2C of all sensors I2C - TIDS, PADS, ITDS and HIDS with basic porting of delay, and added a few not working stuff to do_map like printing AT and AT+CPIN? commands while pressing enter on keyb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
2023-07-31 Working I2C of all sensors I2C - TIDS, PADS, ITDS and HIDS with basic porting of delay, and added a few not working stuff to do_map like printing AT and AT+CPIN? commands while pressing enter on keyb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
2023-08-16 add all sensors working with UART for Pure connection between AMCU and Modem, and connection to host MCU with external UART working with MQTT connection to DPS working

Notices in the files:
parts and their libraries:
155124YS73200A_Eagle_WL-SMSW_rev20a: Copyright: Würth Elektronik
